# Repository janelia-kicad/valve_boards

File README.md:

valve_boards
============

Authors:

    Peter Polidoro <polidorop@janelia.hhmi.org>

License:

    BSD

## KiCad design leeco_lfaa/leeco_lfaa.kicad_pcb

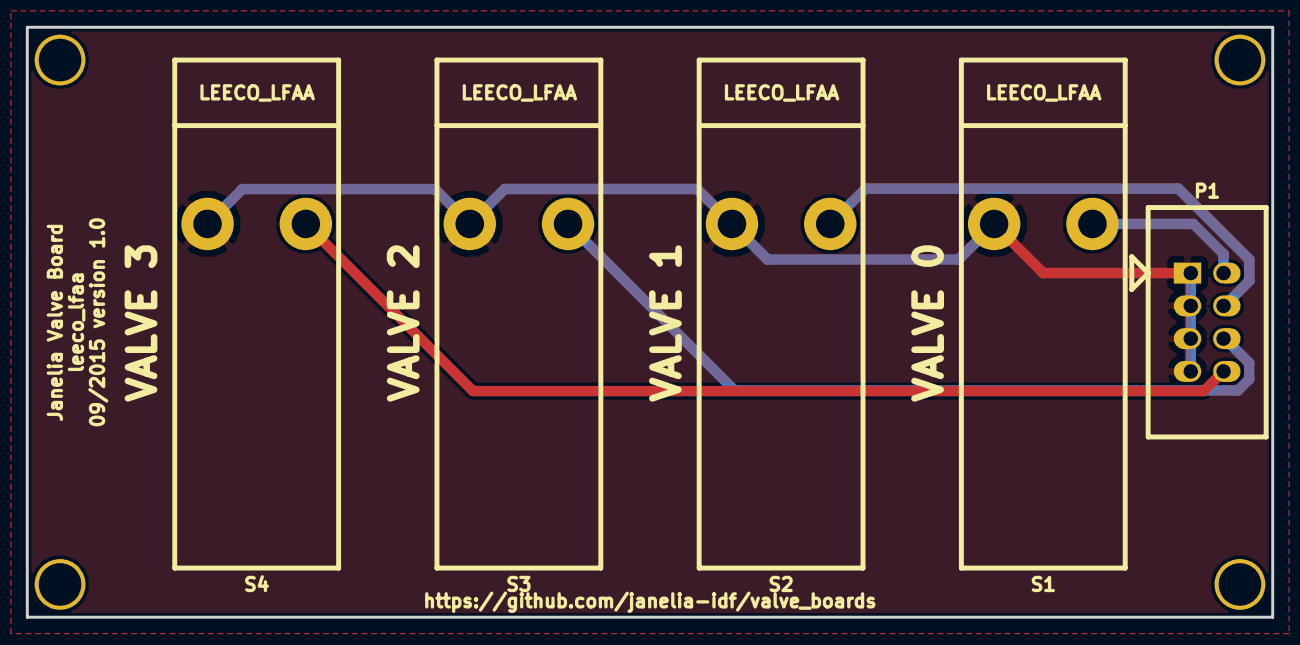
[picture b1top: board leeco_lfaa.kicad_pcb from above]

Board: 2 copper layers, 96.5 x 45.7 mm, 9 parts (0 on the bottom side), 5 nets.

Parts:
MH1, MH2, MH3, MH4: MOUNTING_HOLE
P1: HEADER_02X04; HEADER_02x04
S1, S2, S3, S4: LEECO_LFAA

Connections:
/OUT0: P1.2, S1.2
/OUT1: P1.4, S2.2
/OUT2: P1.6, S3.2
/OUT3: P1.8, S4.2
VAA: P1.1, P1.3, P1.5, P1.7, S1.1, S2.1, S3.1, S4.1

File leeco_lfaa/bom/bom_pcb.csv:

Item,Reference(s),Value,Quantity,Description,PartNumber,Vendor
1,P1,HEADER_02X04,1,CONN HEADER 8POS 2.54,732-5395-ND,digikey
2,S1 S2 S3 S4,LEECO_LFAA,4,CONN RECEPT PIN .032-.046in .240in,ED1013-ND,digikey

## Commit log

2015-09-10 Initial commit.
2015-09-10 Initial leeco_lfaa add.
2015-09-10 Finished leeco_lfaa v1.0.
2015-09-23 Added digikey_order.
2015-09-23 Added ribbon cable parts.
2015-09-29 Added picture.
2015-09-30 Added documentation pictures.
2017-06-15 Removed .cmp file.
2017-09-22 Removed extra libraries.
2017-10-04 Updated LibDir.
2018-01-08 Updated to v4.
2018-01-08 Added v4 files.
2018-01-08 Removed *cache* and *rescue*.
2018-03-09 Update license from software to hardware.
2018-04-12 README.md -> README.org.
2018-04-19 Added .DS_Store to .gitignore.
2018-08-12 Removed v4 files.
2018-08-24 Removed F.SilkS from pads.
2021-09-16 Update email address
2021-09-21 Remove ignored files
2021-09-21 Remove obsolete references
2022-02-22 Add guix files
2022-02-23 Add guix documentation
